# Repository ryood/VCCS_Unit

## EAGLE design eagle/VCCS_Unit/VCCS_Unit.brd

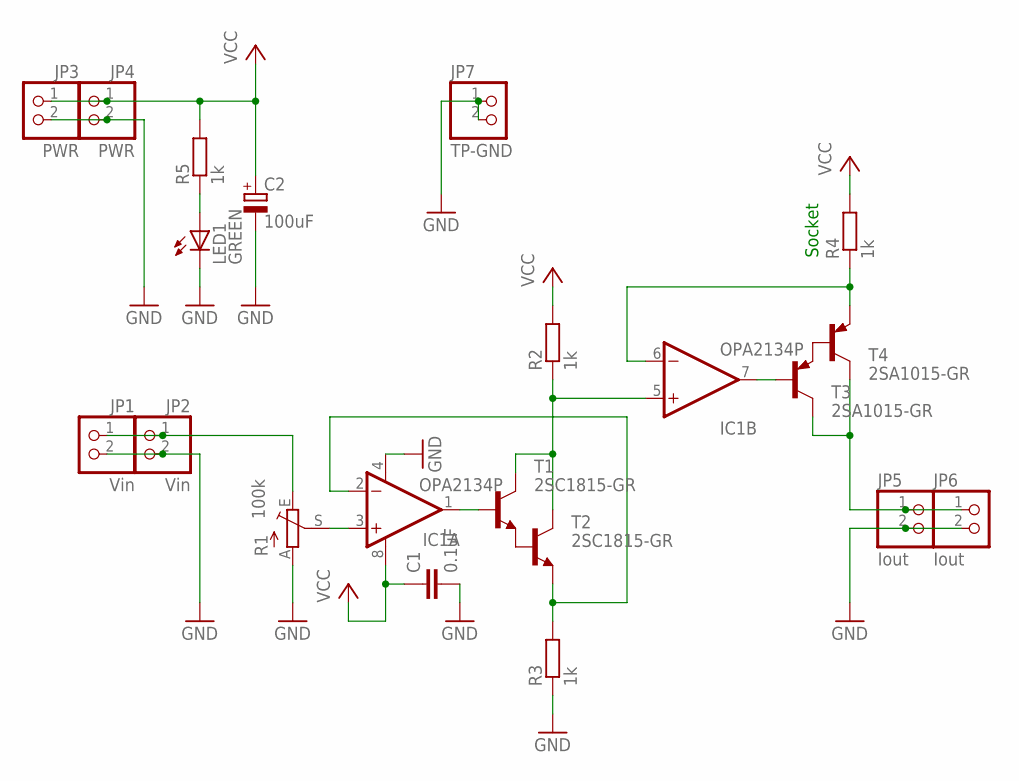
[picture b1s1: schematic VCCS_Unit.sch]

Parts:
C1: 0.1uF; C025-024X044
C2: 100uF; E2,5-7
IC1: OPA2134P; DIL08
JP1, JP2: Vin; 1X02
JP3, JP4: PWR; 1X02
JP5, JP6: Iout; 1X02
JP7: TP-GND; 1X02
LED1: GREEN; LED3MM
R1: 100k; B25P
R2, R3, R4, R5: 1k; 0207/7
T1, T2: 2SC1815-GR; TO92-ECB
T3, T4: 2SA1015-GR; TO92-ECB

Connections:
GND: C1.2, C2.-, IC1.4 (V-), JP1.2, JP2.2, JP3.2, JP4.2, JP5.2, JP6.2, JP7.1, JP7.2, LED1.K (C), R1.A, R3.1
unnamed: T1.E, T2.B
unnamed: T3.E, T4.B
unnamed: IC1.2 (-IN), R3.2, T2.E
unnamed: JP1.1, JP2.1, R1.E
unnamed: IC1.3 (+IN), R1.S
unnamed: IC1.1 (OUT), T1.B
unnamed: IC1.7 (OUT), T3.B
unnamed: JP5.1, JP6.1, T3.C, T4.C
unnamed: IC1.5 (+IN), R2.1, T1.C, T2.C
unnamed: IC1.6 (-IN), R4.1, T4.E
unnamed: LED1.A, R5.1
VCC: C1.1, C2.+, IC1.8 (V+), JP3.1, JP4.1, R2.2, R4.2, R5.2

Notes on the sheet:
Socket

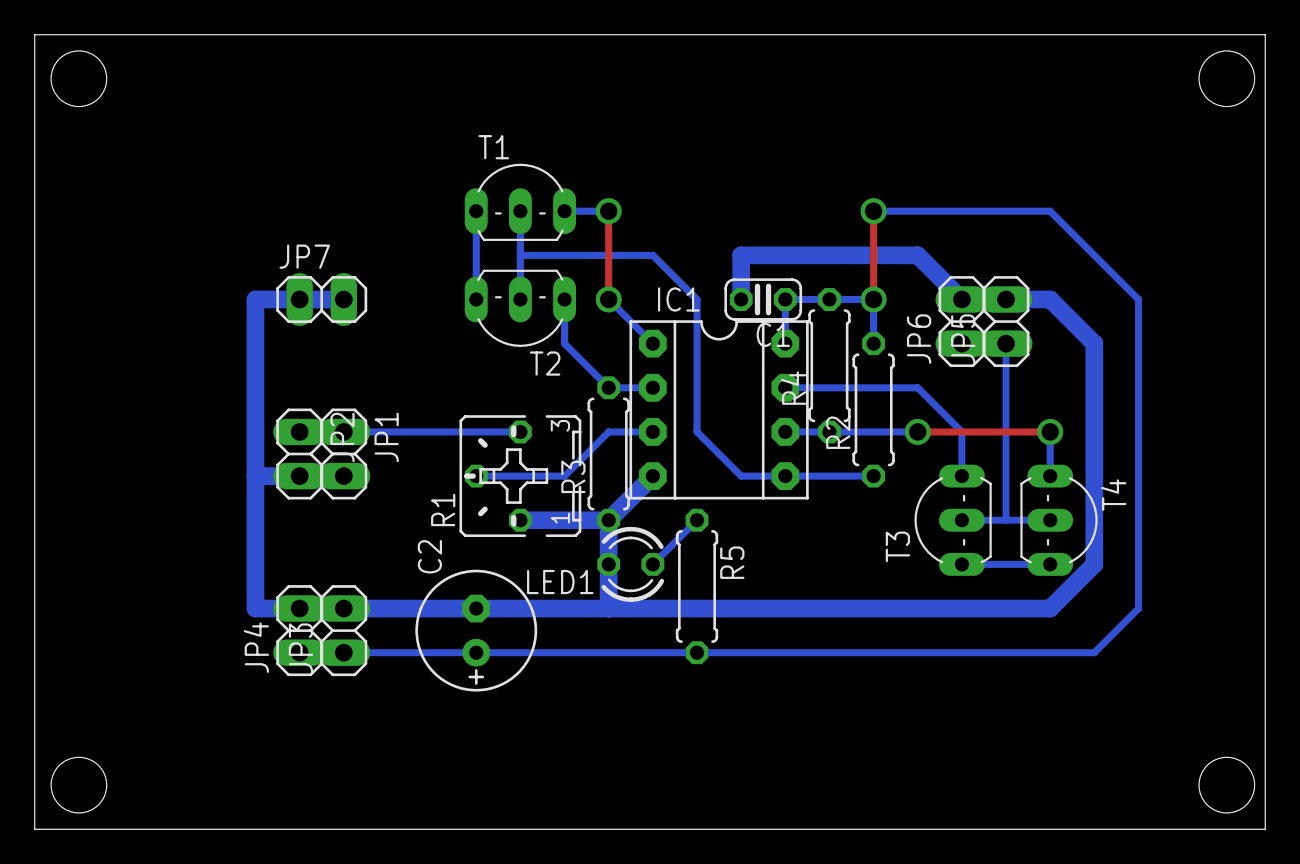
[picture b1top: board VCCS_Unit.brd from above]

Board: 2 copper layers, 70.8 x 45.7 mm, 20 parts (0 on the bottom side), 13 nets.

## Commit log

2017-07-22 Updated: the eagle files
2017-07-23 Add: テスト表
